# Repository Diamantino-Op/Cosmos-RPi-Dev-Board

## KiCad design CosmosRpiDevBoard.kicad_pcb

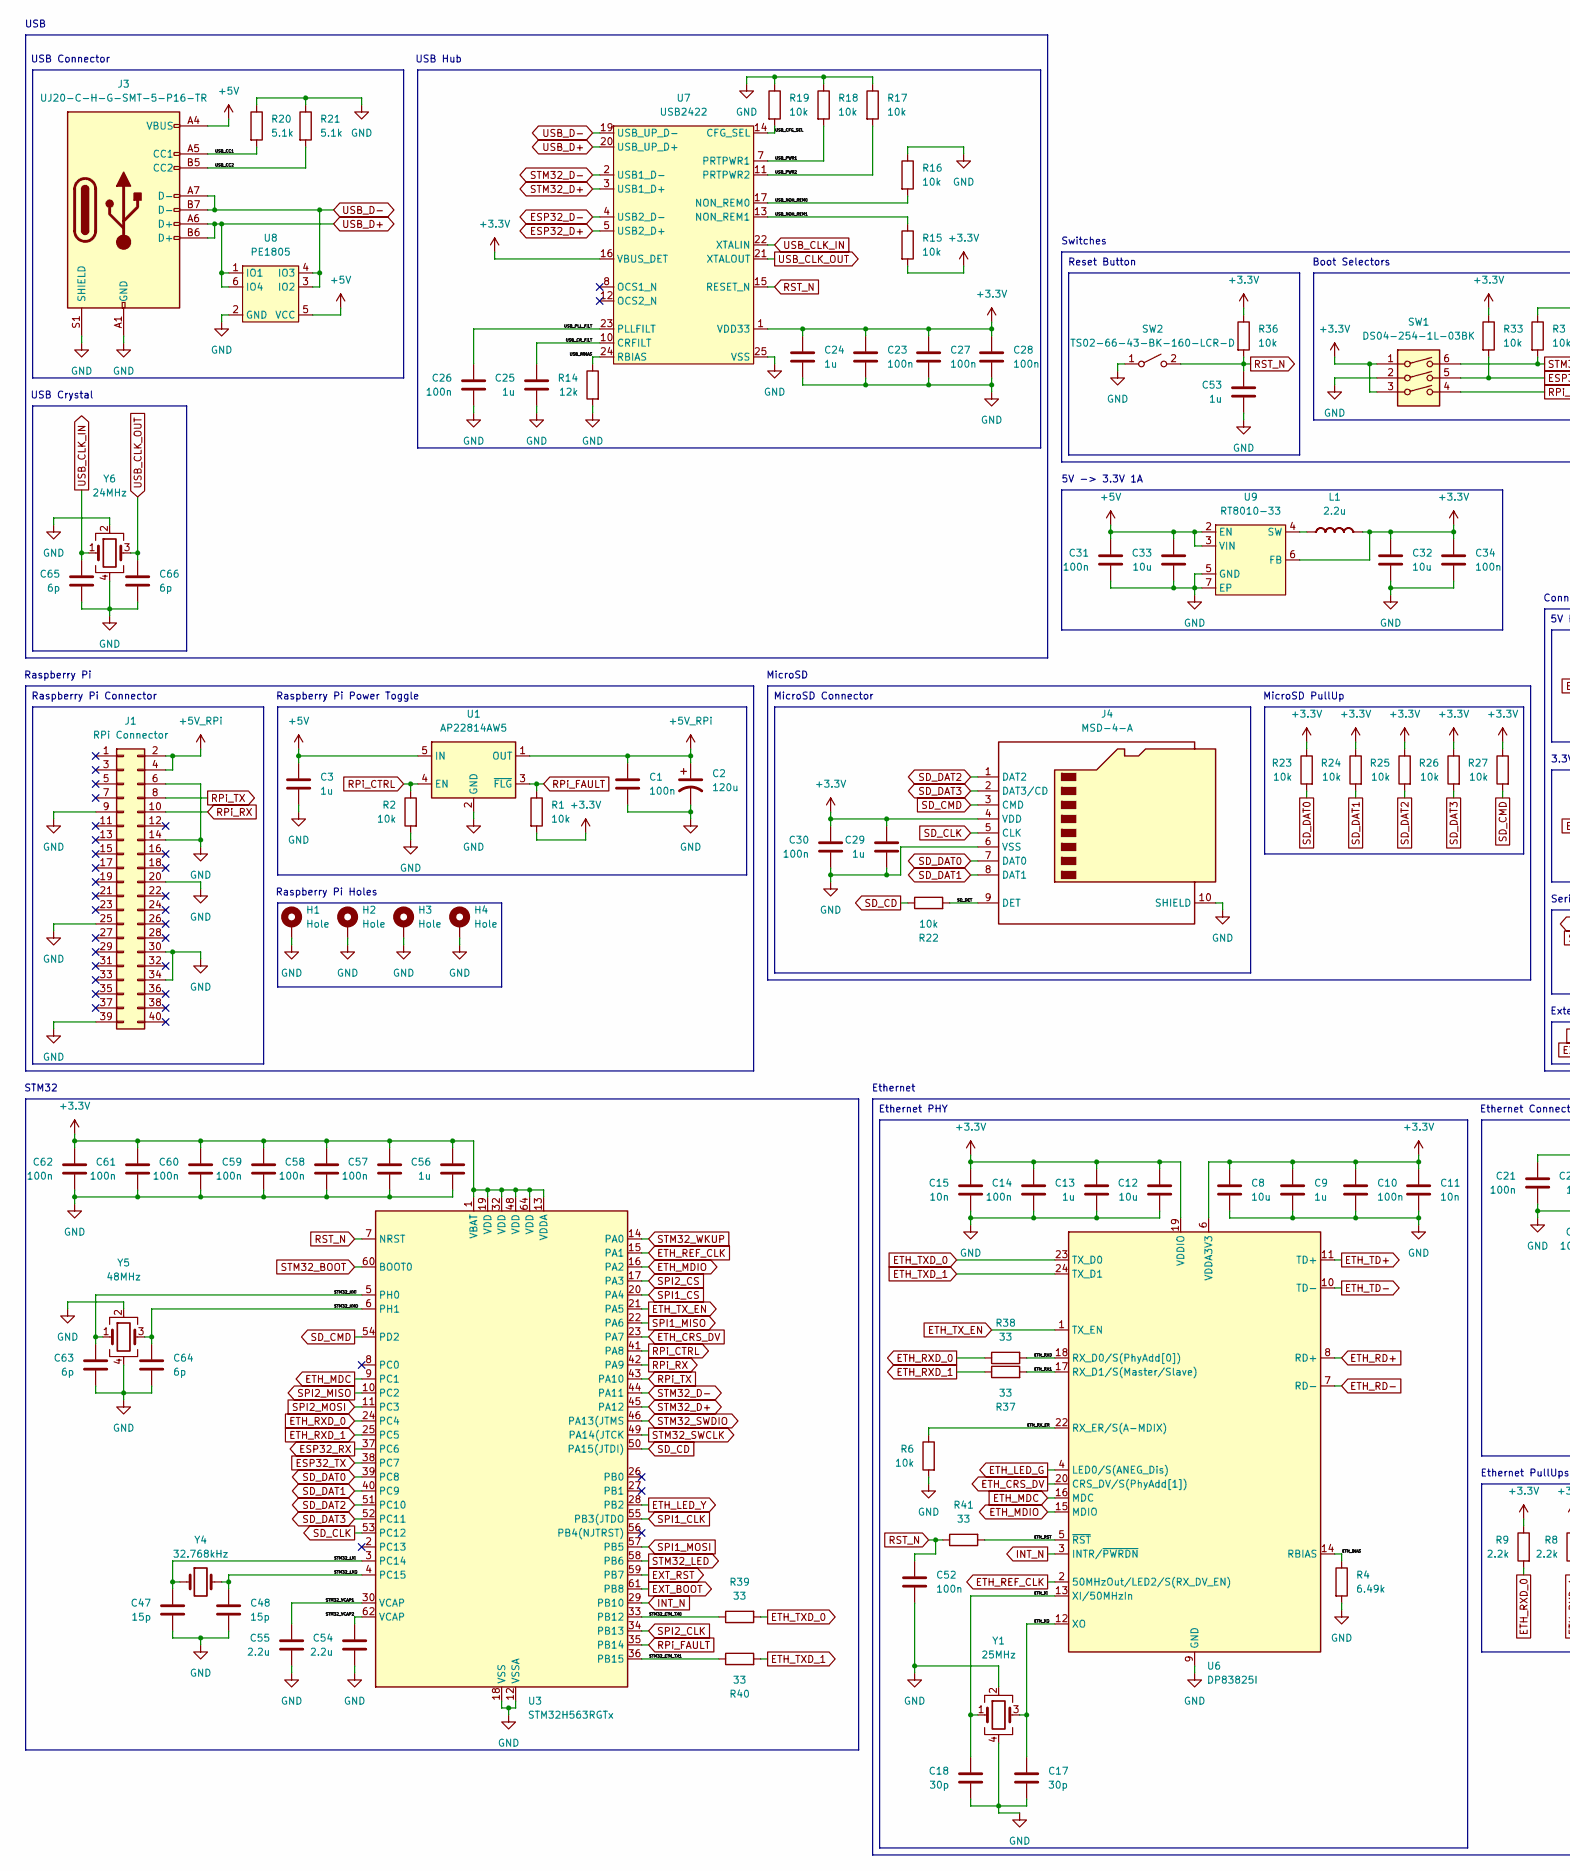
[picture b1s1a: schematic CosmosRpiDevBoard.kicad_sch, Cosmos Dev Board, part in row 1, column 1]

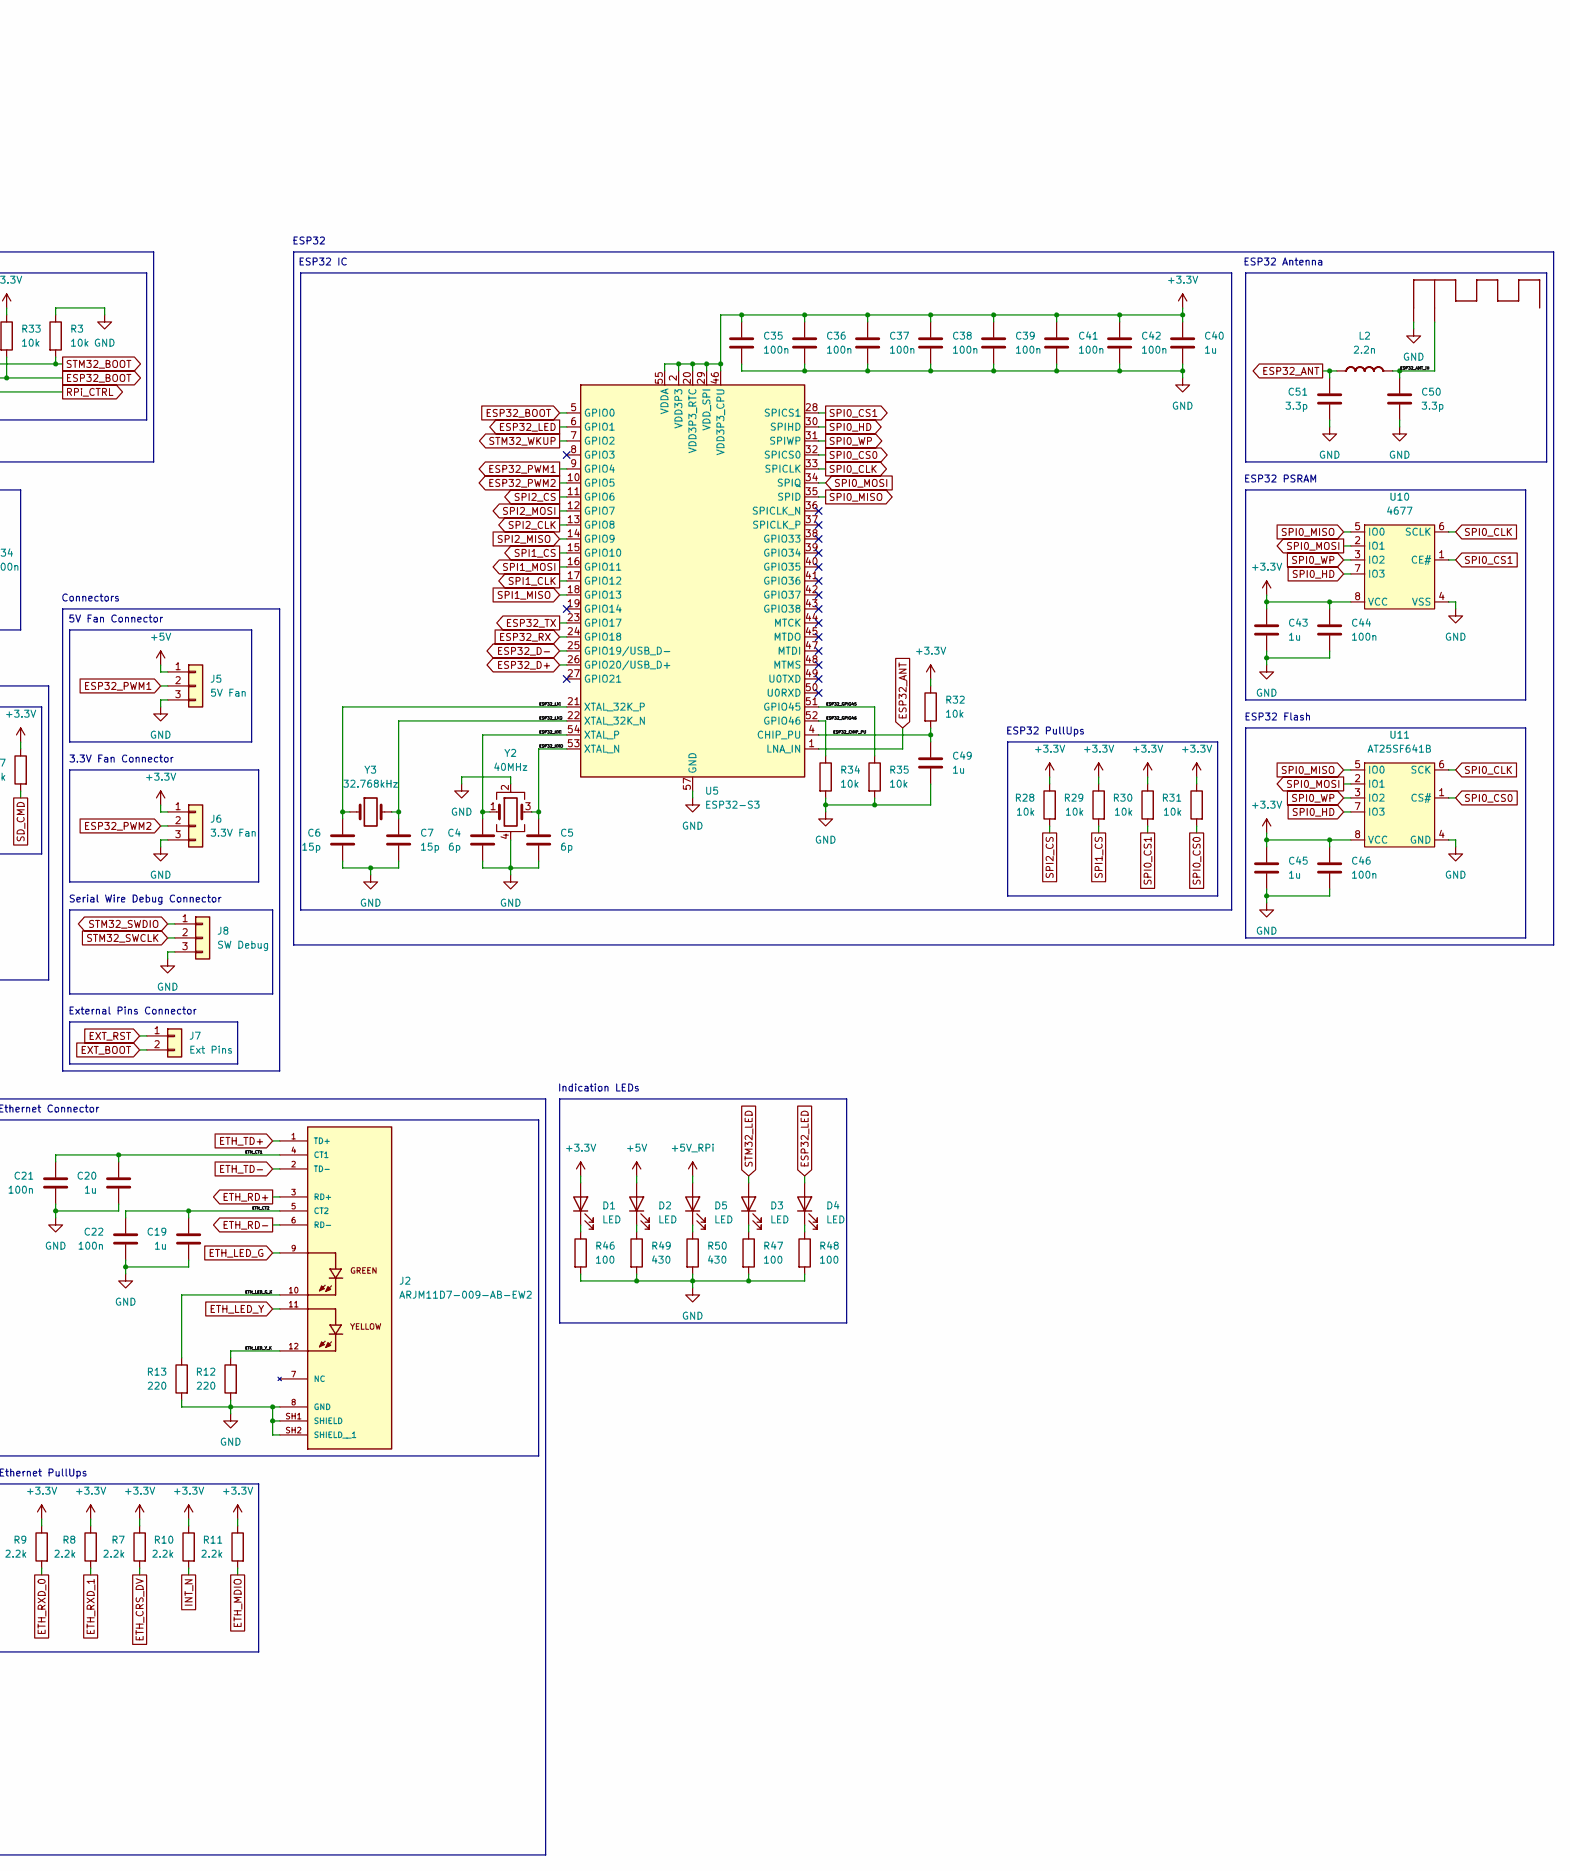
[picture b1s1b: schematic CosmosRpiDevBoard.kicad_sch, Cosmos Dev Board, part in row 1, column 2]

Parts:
C1, C10, C14, C21, C22, C23, C26, C27, C28, C30, C31, C34, C35, C36, C37, C38, C39, C41, C42, C44, C46, C52, C57, C58, C59, C60, C61, C62: 100n; C_0402_1005Metric
C2: 120u; CP_Elec_6.3x5.9
C3, C9, C13, C19, C20, C24, C25, C29, C40, C43, C45, C49, C53, C56: 1u; C_0402_1005Metric
C4, C5, C63, C64, C65, C66: 6p; C_0402_1005Metric
C6, C7, C47, C48: 15p; C_0402_1005Metric
C8, C12, C32, C33: 10u; C_0402_1005Metric
C11, C15: 10n; C_0402_1005Metric
C17, C18: 30p; C_0402_1005Metric
C50, C51: 3.3p; C_0402_1005Metric
C54, C55: 2.2u; C_0402_1005Metric
D1, D2, D3, D4, D5: LED; LED_0603_1608Metric
H1, H2, H3, H4: Hole; RPi_Hole
J1: RPi Connector; PinSocket_2x20_P2.54mm_Vertical
J2: ARJM11D7-009-AB-EW2; PARTREV 03-08-24
J3: UJ20-C-H-G-SMT-5-P16-TR; USB_C_Receptacle_GCT_USB4110
J4: MSD-4-A
J5: 5V Fan; PinHeader_1x03_P2.54mm_Vertical
J6: 3.3V Fan; PinHeader_1x03_P2.54mm_Vertical
J7: Ext Pins; PinHeader_1x02_P2.54mm_Vertical
J8: SW Debug; PinHeader_1x03_P2.54mm_Vertical
L1: 2.2u; L_0806_2016Metric; Rating A
L2: 2.2n; L_0402_1005Metric; Rating A
R1, R2, R3, R6, R15, R16, R17, R18, R19, R22, R23, R24, R25, R26, R27, R28, R29, R30, R31, R32, R33, R34, R35, R36: 10k; R_0402_1005Metric
R4: 6.49k; R_0402_1005Metric
R7, R8, R9, R10, R11: 2.2k; R_0402_1005Metric
R12, R13: 220; R_0402_1005Metric
R14: 12k; R_0402_1005Metric
R20, R21: 5.1k; R_0402_1005Metric
R37, R38, R39, R40, R41: 33; R_0402_1005Metric
R46, R47, R48: 100; R_0402_1005Metric
R49, R50: 430; R_0402_1005Metric
SW1: DS04-254-1L-03BK; SW_DIP_SPSTx03_Slide_6.7x9.18mm_W7.62mm_P2.54mm_LowProfile
SW2: TS02-66-43-BK-160-LCR-D; SW_PUSH_6mm_H4.3mm
U1: AP22814AW5; SOT-23-5
U2: Texas_SWRA117D_2.4GHz_Right
U3: STM32H563RGTx; LQFP-64_10x10mm_P0.5mm
U5: ESP32-S3; QFN-56-1EP_7x7mm_P0.4mm_EP4x4mm
U6: DP83825I; Texas_RMQ0024A_WQFN-24-1EP_3x3mm_P0.4mm_EP1.9x1.9mm
U7: USB2422; QFN-24-1EP_4x4mm_P0.5mm_EP2.5x2.5mm
U8: PE1805; SOT-23-6
U9: RT8010-33; RT8010
U10: 4677; SOIC-8_3.9x4.9mm_P1.27mm
U11: AT25SF641B; SOIC-8_5.3x5.3mm_P1.27mm
Y1: 25MHz; Crystal_SMD_3225-4Pin_3.2x2.5mm
Y2: 40MHz; Crystal_SMD_3225-4Pin_3.2x2.5mm
Y3, Y4: 32.768kHz; Crystal_Round_D2.0mm_Vertical
Y5: 48MHz; Crystal_SMD_3225-4Pin_3.2x2.5mm
Y6: 24MHz; Crystal_SMD_3225-4Pin_3.2x2.5mm

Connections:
+3.3V: C8.1, C9.1, C10.1, C11.1, C12.1, C13.1, C14.1, C15.1, C23.1, C24.1, C27.1, C28.1, C29.1, C30.1, C32.1, C34.1, C35.1, C36.1, C37.1, C38.1, C39.1, C40.1, C41.1, C42.1, C43.1, C44.1, C45.1, C46.1, C56.1, C57.1, C58.1, C59.1, C60.1, C61.1, C62.1, D1.2 (A), J4.4 (VDD), J6.1, L1.2 (-), R1.2, R7.1, R8.1, R9.1, R10.1, R11.1, R15.2, R23.1, R24.1, R25.1, R26.1, R27.1, R28.1, R29.1, R30.1, R31.1, R32.1, R33.1, R36.1, SW1.1, SW1.3, U3.1 (VBAT), U3.13 (VDDA), U3.19 (VDD), U3.32 (VDD), U3.48 (VDD), U3.64 (VDD), U5.2 (VDD3P3), U5.3 (VDD3P3), U5.20 (VDD3P3_RTC), U5.29 (VDD_SPI), U5.46 (VDD3P3_CPU), U5.55 (VDDA), U5.56 (VDDA), U6.6 (VDDA3V3), U6.19 (VDDIO), U7.1 (VDD33), U7.9 (VDD33), U7.16 (VBUS_DET), U7.18 (VDD33), U9.6 (FB), U10.8 (VCC), U11.8 (VCC)
+5V: C3.1, C31.1, C33.1, D2.2 (A), J3.A4 (VBUS), J3.A9 (VBUS), J3.B4 (VBUS), J3.B9 (VBUS), J5.1, U1.5 (IN), U8.5 (VCC), U9.2 (EN), U9.3 (VIN)
+5V_RPi: C1.1, C2.1, D5.2 (A), J1.2, J1.4, U1.1 (OUT)
/ESP32_ANT_IN: C50.1, L2.2 (-), U2.1
/ESP32_CHIP_PU: C49.1, R32.2, U5.4 (CHIP_PU)
/ESP32_GPIO45: R35.1, U5.51 (GPIO45)
/ESP32_GPIO46: R34.1, U5.52 (GPIO46)
/ESP32_HXI: C4.1, U5.54 (XTAL_P), Y2.1
/ESP32_HXO: C5.1, U5.53 (XTAL_N), Y2.3
/ESP32_LXI: C6.1, U5.21 (XTAL_32K_P), Y3.1
/ESP32_LXO: C7.1, U5.22 (XTAL_32K_N), Y3.2
/ETH_BIAS: R4.1, U6.14 (RBIAS)
/ETH_CT1: C20.1, C21.1, J2.4 (CT1)
/ETH_CT2: C19.1, C22.1, J2.5 (CT2)
/ETH_LED_G_K: J2.10, R13.1
/ETH_LED_Y_K: J2.12, R12.1
/ETH_RST: R41.2, U6.5 (~RST)
/ETH_RX0: R38.2, U6.18 (RX_D0/S(PhyAdd[0]))
/ETH_RX1: R37.2, U6.17 (RX_D1/S(Master/Slave))
/ETH_RX_ER: R6.1, U6.22 (RX_ER/S(A-MDIX))
/ETH_XI: C18.1, U6.13 (XI/50MHzIn), Y1.1
/ETH_XO: C17.1, U6.12 (XO), Y1.3
/SD_DET: J4.9 (DET), R22.2
/STM32_ETH_TX0: R39.1, U3.33 (PB12)
/STM32_ETH_TX1: R40.1, U3.36 (PB15)
/STM32_HXI: C63.1, U3.5 (PH0), Y5.1
/STM32_HXO: C64.1, U3.6 (PH1), Y5.3
/STM32_LXI: C47.1, U3.3 (PC14), Y4.1
/STM32_LXO: C48.1, U3.4 (PC15), Y4.2
/STM32_VCAP1: C55.1, U3.30 (VCAP)
/STM32_VCAP2: C54.1, U3.62 (VCAP)
/USB_CC1: J3.A5 (CC1), R20.2
/USB_CC2: J3.B5 (CC2), R21.2
/USB_CFG_SEL: R19.2, U7.14 (CFG_SEL)
/USB_CR_FILT: C25.1, U7.10 (CRFILT)
/USB_NON_REM0: R16.2, U7.17 (NON_REM0)
/USB_NON_REM1: R15.1, U7.13 (NON_REM1)
/USB_PLL_FILT: C26.1, U7.23 (PLLFILT)
/USB_PWR1: R18.2, U7.7 (PRTPWR1)
/USB_PWR2: R17.2, U7.11 (PRTPWR2)
/USB_RBIAS: R14.1, U7.24 (RBIAS)
ESP32_ANT: C51.1, L2.1 (+), U5.1 (LNA_IN)
ESP32_BOOT: R33.2, SW1.5, U5.5 (GPIO0)
ESP32_D+: U5.26 (GPIO20/USB_D+), U7.5 (USB2_D+)
ESP32_D-: U5.25 (GPIO19/USB_D-), U7.4 (USB2_D-)
ESP32_LED: D4.2 (A), U5.6 (GPIO1)
ESP32_PWM1: J5.2, U5.9 (GPIO4)
ESP32_PWM2: J6.2, U5.10 (GPIO5)
ESP32_RX: U3.37 (PC6), U5.24 (GPIO18)
ESP32_TX: U3.38 (PC7), U5.23 (GPIO17)
ETH_CRS_DV: R7.2, U3.23 (PA7), U6.20 (CRS_DV/S(PhyAdd[1]))
ETH_LED_G: J2.9, U6.4 (LED0/S(ANEG_Dis))
ETH_LED_Y: J2.11, U3.28 (PB2)
ETH_MDC: U3.9 (PC1), U6.16 (MDC)
ETH_MDIO: R11.2, U3.16 (PA2), U6.15 (MDIO)
ETH_RD+: J2.3 (RD+), U6.8 (RD+)
ETH_RD-: J2.6 (RD-), U6.7 (RD-)
ETH_REF_CLK: U3.15 (PA1), U6.2 (50MHzOut/LED2/S(RX_DV_EN))
ETH_RXD_0: R9.2, R38.1, U3.24 (PC4)
ETH_RXD_1: R8.2, R37.1, U3.25 (PC5)
ETH_TD+: J2.1 (TD+), U6.11 (TD+)
ETH_TD-: J2.2 (TD-), U6.10 (TD-)
ETH_TXD_0: R39.2, U6.23 (TX_D0)
ETH_TXD_1: R40.2, U6.24 (TX_D1)
ETH_TX_EN: U3.21 (PA5), U6.1 (TX_EN)
EXT_BOOT: J7.2, U3.61 (PB8)
EXT_RST: J7.1, U3.59 (PB7)
GND: C1.2, C2.2, C3.2, C4.2, C5.2, C6.2, C7.2, C8.2, C9.2, C10.2, C11.2, C12.2, C13.2, C14.2, C15.2, C17.2, C18.2, C19.2, C20.2, C21.2, C22.2, C23.2, C24.2, C25.2, C26.2, C27.2, C28.2, C29.2, C30.2, C31.2, C32.2, C33.2, C34.2, C35.2, C36.2, C37.2, C38.2, C39.2, C40.2, C41.2, C42.2, C43.2, C44.2, C45.2, C46.2, C47.2, C48.2, C49.2, C50.2, C51.2, C52.2, C53.2, C54.2, C55.2, C56.2, C57.2, C58.2, C59.2, C60.2, C61.2, C62.2, C63.2, C64.2, C65.2, C66.2, H1.1, H2.1, H3.1, H4.1, J1.6, J1.9, J1.14, J1.20, J1.25, J1.30, J1.34, J1.39, J2.8 (GND), J2.SH1 (SHIELD), J2.SH2 (SHIELD__1), J3.A1 (GND), J3.A12 (GND), J3.B1 (GND), J3.B12 (GND), J3.S1 (SHIELD), J4.6 (VSS), J4.10 (SHIELD), J5.3, J6.3, J8.3, R2.2, R3.1, R4.2, R6.2, R12.2, R13.2, R14.2, R16.1, R17.1, R18.1, R19.1, R20.1, R21.1, R34.2, R35.2, R46.2, R47.2, R48.2, R49.2, R50.2, SW1.2, SW2.1 (A), U1.2 (GND), U2.2, U3.12 (VSSA), U3.18 (VSS), U3.31 (VSS), U3.47 (VSS), U3.63 (VSS), U5.57 (GND), U6.9 (GND), U6.21 (GND), U6.25 (GND), U7.25 (VSS), U8.2 (GND), U9.5 (GND), U9.7 (EP), U10.4 (VSS), U11.4 (GND), Y1.2, Y1.4, Y2.2, Y2.4, Y5.2, Y5.4, Y6.2, Y6.4
INT_N: R10.2, U3.29 (PB10), U6.3 (INTR/~PWRDN)
unnamed: D1.1 (K), R46.1
unnamed: D2.1 (K), R49.1
unnamed: D3.1 (K), R47.1
unnamed: D4.1 (K), R48.1
unnamed: D5.1 (K), R50.1
unnamed: L1.1 (+), U9.4 (SW)
RPi_CTRL: R2.1, SW1.4, U1.4 (EN), U3.41 (PA8)
RPi_FAULT: R1.1, U1.3 (~FLG), U3.35 (PB14)
RPi_RX: J1.10, U3.42 (PA9)
RPi_TX: J1.8, U3.43 (PA10)
RST_N: C52.1, C53.1, R36.2, R41.1, SW2.2 (B), U3.7 (NRST), U7.15 (RESET_N)
SD_CD: R22.1, U3.50 (PA15(JTDI))
SD_CLK: J4.5 (CLK), U3.53 (PC12)
SD_CMD: J4.3 (CMD), R27.2, U3.54 (PD2)
SD_DAT0: J4.7 (DAT0), R23.2, U3.39 (PC8)
SD_DAT1: J4.8 (DAT1), R24.2, U3.40 (PC9)
SD_DAT2: J4.1 (DAT2), R25.2, U3.51 (PC10)
SD_DAT3: J4.2 (DAT3/CD), R26.2, U3.52 (PC11)
SPI0_CLK: U5.33 (SPICLK), U10.6 (SCLK), U11.6 (SCK)
SPI0_CS0: R31.2, U5.32 (SPICS0), U11.1 (CS#)
SPI0_CS1: R30.2, U5.28 (SPICS1), U10.1 (CE#)
SPI0_HD: U5.30 (SPIHD), U10.7 (IO3), U11.7 (IO3)
SPI0_MISO: U5.35 (SPID), U10.5 (IO0), U11.5 (IO0)
SPI0_MOSI: U5.34 (SPIQ), U10.2 (IO1), U11.2 (IO1)
SPI0_WP: U5.31 (SPIWP), U10.3 (IO2), U11.3 (IO2)
SPI1_CLK: U3.55 (PB3(JTDO), U5.17 (GPIO12)
SPI1_CS: R29.2, U3.20 (PA4), U5.15 (GPIO10)
SPI1_MISO: U3.22 (PA6), U5.18 (GPIO13)
SPI1_MOSI: U3.57 (PB5), U5.16 (GPIO11)
SPI2_CLK: U3.34 (PB13), U5.13 (GPIO8)
SPI2_CS: R28.2, U3.17 (PA3), U5.11 (GPIO6)
SPI2_MISO: U3.10 (PC2), U5.14 (GPIO9)
SPI2_MOSI: U3.11 (PC3), U5.12 (GPIO7)
STM32_BOOT: R3.2, SW1.6, U3.60 (BOOT0)
STM32_D+: U3.45 (PA12), U7.3 (USB1_D+)
STM32_D-: U3.44 (PA11), U7.2 (USB1_D-)
STM32_LED: D3.2 (A), U3.58 (PB6)
STM32_SWCLK: J8.2, U3.49 (PA14(JTCK)
STM32_SWDIO: J8.1, U3.46 (PA13(JTMS)
STM32_WKUP: U3.14 (PA0), U5.7 (GPIO2)
USB_CLK_IN: C65.1, U7.22 (XTALIN), Y6.1
USB_CLK_OUT: C66.1, U7.21 (XTALOUT), Y6.3
USB_D+: J3.A6 (D+), J3.B6 (D+), U7.20 (USB_UP_D+), U8.1 (IO1), U8.6 (IO4)
USB_D-: J3.A7 (D-), J3.B7 (D-), U7.19 (USB_UP_D-), U8.3 (IO2), U8.4 (IO3)

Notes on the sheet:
Boot Selectors
USB Crystal
Reset Button
Raspberry Pi Connector
Serial Wire Debug Connector
Switches
Raspberry Pi
5V -> 3.3V 1A
ESP32
ESP32 Antenna
Connectors
Raspberry Pi Power Toggle
Ethernet PullUps
USB Connector
USB
MicroSD
USB Hub
5V Fan Connector
MicroSD PullUp
Raspberry Pi Holes
Ethernet PHY
MicroSD Connector
Indication LEDs
ESP32 IC
Ethernet
Ethernet Connector
External Pins Connector
ESP32 Flash
3.3V Fan Connector
STM32
ESP32 PSRAM
ESP32 PullUps

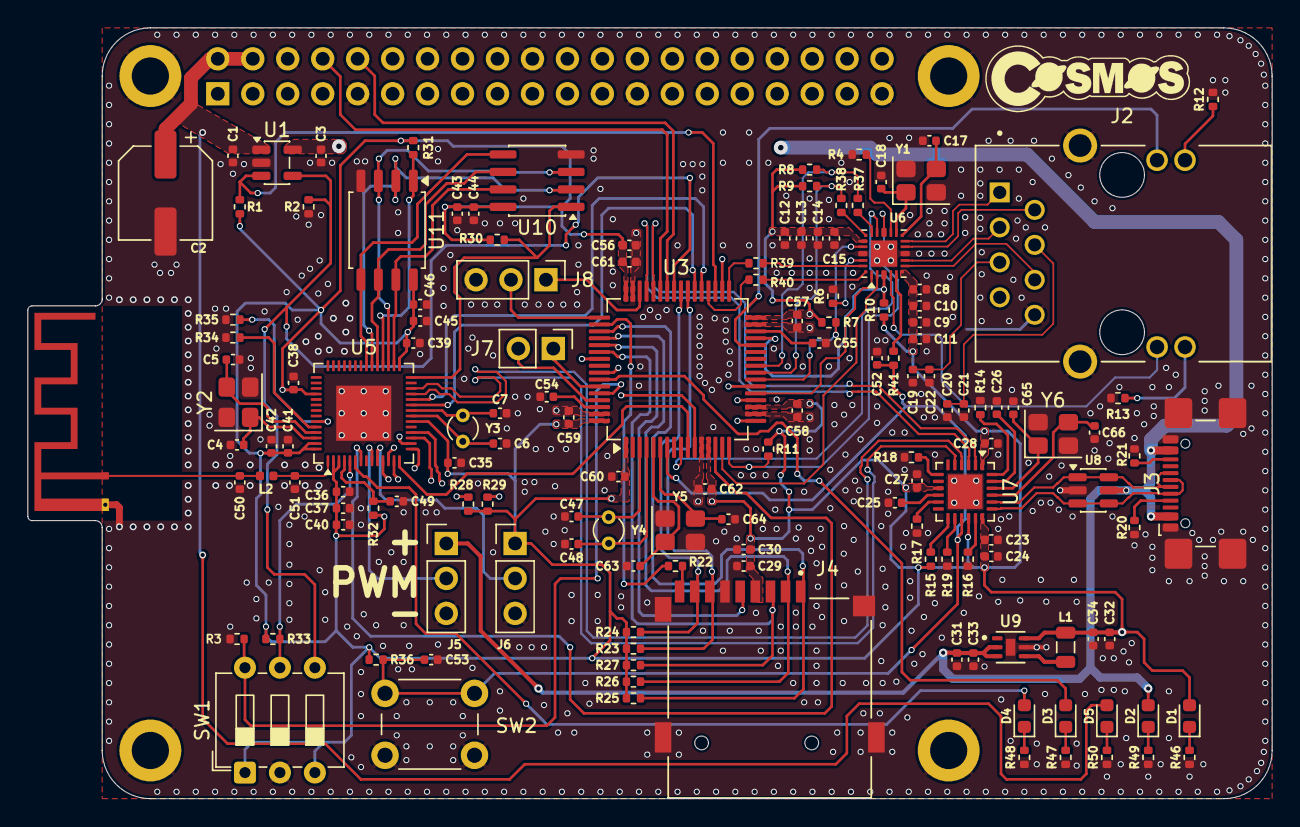
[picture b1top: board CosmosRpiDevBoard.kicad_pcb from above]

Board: 4 copper layers, 90.4 x 56.0 mm, 147 parts (1 on the bottom side), 113 nets.

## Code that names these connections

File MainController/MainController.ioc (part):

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Mcu.Name=STM32H563RGTx
Mcu.Package=LQFP64
Mcu.UserName=STM32H563RGTx
PA0.Mode=WakeUp1
PA0.Signal=PWR_WKUP1
PA1.Mode=RMII
PA1.Signal=ETH_REF_CLK
PA10.Mode=Asynchronous
PA10.Signal=USART1_RX
PA11.Mode=Device
PA11.Signal=USB_DM
PA12.Mode=Device
PA12.Signal=USB_DP
PA13(JTMS/SWDIO).Mode=Serial_Wire
PA13(JTMS/SWDIO).Signal=DEBUG_JTMS-SWDIO
PA14(JTCK/SWCLK).Mode=Serial_Wire
PA14(JTCK/SWCLK).Signal=DEBUG_JTCK-SWCLK
PA15(JTDI).GPIOParameters=GPIO_PuPd,GPIO_Label
PA15(JTDI).GPIO_Label=SDMMC_CD
PA15(JTDI).GPIO_PuPd=GPIO_PULLUP
PA15(JTDI).Signal=GPIO_Input
PA2.Mode=RMII
PA2.Signal=ETH_MDIO
PA3.Mode=NSS_Signal_Hard_Input
PA3.Signal=SPI2_NSS
PA4.Mode=NSS_Signal_Hard_Input
PA4.Signal=SPI1_NSS
PA5.Mode=RMII
PA5.Signal=ETH_TX_EN
PA6.Mode=Full_Duplex_Slave
PA6.Signal=SPI1_MISO
PA7.Mode=RMII
PA7.Signal=ETH_CRS_DV
PA9.Mode=Asynchronous
PA9.Signal=USART1_TX
PB10.GPIOParameters=GPIO_Label
PB10.GPIO_Label=ETH_INT
PB10.Signal=GPIO_Input
PB12.Mode=RMII
PB12.Signal=ETH_TXD0
PB13.Mode=Full_Duplex_Slave
PB13.Signal=SPI2_SCK
PB14.GPIOParameters=GPIO_Label
PB14.GPIO_Label=RPi_FAULT
PB14.Signal=GPIO_Input
PB15.Mode=RMII
PB15.Signal=ETH_TXD1
PB2.GPIOParameters=GPIO_Label
PB2.GPIO_Label=ETH_LED_Y
PB2.Signal=GPIO_Output
PB3(JTDO/TRACESWO).Mode=Full_Duplex_Slave
PB3(JTDO/TRACESWO).Signal=SPI1_SCK
PB4(NJTRST).GPIOParameters=GPIO_Label
PB4(NJTRST).GPIO_Label=RPi_CTRL
PB4(NJTRST).Signal=GPIO_Output
PB5.Mode=Full_Duplex_Slave
PB5.Signal=SPI1_MOSI
PB6.GPIOParameters=GPIO_Label
PB6.GPIO_Label=STATUS_LED
PB6.Signal=GPIO_Output
PB7.GPIOParameters=GPIO_Label
PB7.GPIO_Label=EXT_RST
PB7.Signal=GPIO_Output
PB8.GPIOParameters=GPIO_Label
PB8.GPIO_Label=EXT_BOOT
PB8.Signal=GPIO_Output
PC1.Mode=RMII
PC1.Signal=ETH_MDC
PC10.Mode=SD_4_bits_Wide_bus
PC10.Signal=SDMMC1_D2
PC11.Mode=SD_4_bits_Wide_bus
PC11.Signal=SDMMC1_D3
PC12.Mode=SD_4_bits_Wide_bus
PC12.Signal=SDMMC1_CK
PC14-OSC32_IN(OSC32_IN).Mode=LSE-External-Oscillator
PC14-OSC32_IN(OSC32_IN).Signal=RCC_OSC32_IN
PC15-OSC32_OUT(OSC32_OUT).Mode=LSE-External-Oscillator
PC15-OSC32_OUT(OSC32_OUT).Signal=RCC_OSC32_OUT
PC2.Mode=Full_Duplex_Slave
PC2.Signal=SPI2_MISO
PC3.Mode=Full_Duplex_Slave
PC3.Signal=SPI2_MOSI
PC4.Mode=RMII
PC4.Signal=ETH_RXD0
PC5.Mode=RMII
PC5.Signal=ETH_RXD1
PC6.Mode=Asynchronous
PC6.Signal=USART6_TX
PC7.Mode=Asynchronous
PC7.Signal=USART6_RX
PC8.Mode=SD_4_bits_Wide_bus
PC8.Signal=SDMMC1_D0
PC9.Mode=SD_4_bits_Wide_bus
PC9.Signal=SDMMC1_D1
PD2.Mode=SD_4_bits_Wide_bus
PD2.Signal=SDMMC1_CMD
PH0-OSC_IN(PH0).Mode=HSE-External-Oscillator
PH0-OSC_IN(PH0).Signal=RCC_OSC_IN
PH1-OSC_OUT(PH1).Mode=HSE-External-Oscillator
PH1-OSC_OUT(PH1).Signal=RCC_OSC_OUT
RCC.HSE_VALUE=48000000
RCC.SYSCLKFreq_VALUE=250000000
RCC.SYSCLKSource=RCC_SYSCLKSOURCE_PLLCLK
board=custom
